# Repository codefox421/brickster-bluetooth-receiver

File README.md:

# BricksTer &ndash; Bluetooth Receiver

&nbsp;&nbsp;&nbsp;

The BricksTer Bluetooth Receiver lets you wirelessly control your LEGO creations from a smart phone, tablet, or PC. It is compatible with the NXT programmable brick. This repository houses the Eagle CAD schematic and design files for the printed circuit board along with the firmware for the receiver.

## Getting Started

### Part List

Components can be ordered from any distributor (e.g. DigiKey, Mouser, etc).
[Please see the Bill of Materials for the list of components.](https://github.com/BTbricks/brickster-bluetooth-receiver/blob/master/8884bt%20Remote%20Control%20Receiver/board/BOM.md)

The rev. 2 board can be purchased from OSH Park.
[Click here to view the OSH Park project page.](https://oshpark.com/shared_projects/jNrizzs2)

### Programming the Board

Once your board is soldered, use the Arduino IDE to load the firmware onto the microcontroller.
The IDE is available for free and can be downloaded from http://arduino.cc/main/software

#### Setting up the Arduino Environment

The microcontroller is an ATtiny84, which is not regularly supported by the Arduino IDE.
[Please visit the Arduino support page to learn more about using Arduino with the ATtiny84.](http://playground.arduino.cc/Main/ArduinoOnOtherAtmelChips)

Download the [Attiny 44/45/84/85 files](https://github.com/damellis/attiny/archive/master.zip) and extract them to `{ARDUINO}/hardware/`, where `{ARDUINO}` represents the directory into which the Arduino IDE and supporting files have been installed. Once completed, your directory should look like this:

```
{ARDUINO}
└-hardware
  └-attiny
    ├-boards.txt
    └-variants
      ├-tiny8
      | └-pins_arduino.h
      └-tiny14
        └-pins_arduino.h
```

#### Burning the "Bootloader"

The ATtiny84 comes from the factory running on an internal 1 MHz clock. In order to run the BricksTer firmware, the ATtiny84 must be told to use its interal 8 MHz clock.

* Connect your board to your computer via the programmer
* Apply power to the power-in Power Functions wire
* Open the Arduino IDE
* Ensure you have selected the proper serial port (`Tools > Serial Port`) and can communicate with the microcontroller
* Select `Tools > Board > ATtiny84 (internal 8 Mhz clock)`
* Select `Tools > Burn Bootloader`
* Wait for the programmer to finish, the IDE should display a success message

#### Loading the Firmware

* Connect your board to your computer via the programmer
* Apply power to the power-in Power Functions wire
* Open the Arduino IDE
* Ensure you have selected the proper serial port (`Tools > Serial Port`) and can communicate with the microcontroller
* Select `Tools > Board > ATtiny84 (internal 8 Mhz clock)`
* Open the firmware file, [`brickster8884bt.ino`](https://github.com/BTbricks/brickster-bluetooth-receiver/blob/master/8884bt%20Remote%20Control%20Receiver/firmware/brickster8884bt.ino)
* Click the Upload button on the Arduino IDE (circle with a right-pointing arrow)
* Wait for the the IDE and programmer to finish, the IDE should display a success message

Note: Use of a Atmel AVRISPmk2 programmer is strongly advised. Other programmers have been known to work, but we can only provide support for the AVRISPmk2.

### File Formats

Design files are created in CadSoft Eagle PCB Design Software.
A free version of the software can be downloaded from www.cadsoftusa.com

&nbsp;&nbsp;&nbsp;

## Ordering the PCB

You can order the unpopulated printed circuit board from OSH Park by following the link below.

<a href="https://oshpark.com/shared_projects/tWWWgV0f"></img></a>

## Distribution License

Where possible, this project uses the MIT license. [Please see the license file for full details.](https://github.com/BTbricks/brickster-bluetooth-receiver/blob/master/LICENSE)

## Contributing

The project is open to all issues and pull requests.
If you have any other questions or feedback, please [contact the project maintainers](https://github.com/orgs/BTbricks/members).

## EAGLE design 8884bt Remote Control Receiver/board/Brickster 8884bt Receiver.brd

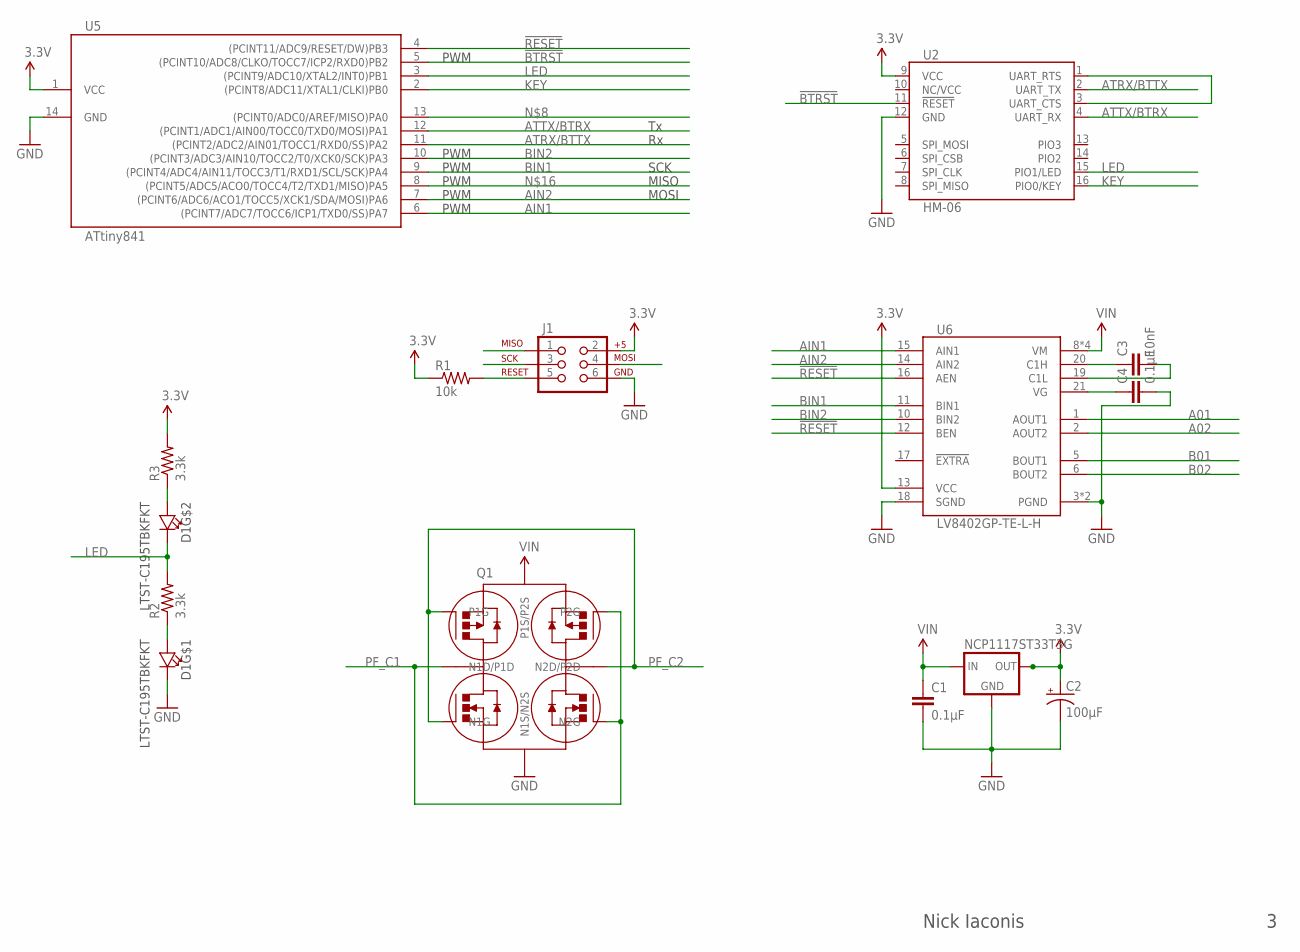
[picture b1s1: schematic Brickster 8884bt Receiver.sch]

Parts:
C1, C4: 0.1µF; 0402
C2: 100µF; 1206
C3: 10nF; 0402
D1: LTST-C195TBKFKT; CHIP-LTST
J1: AVR_SPI_PRG_6NS; 2X3-NS
NCP1117ST33T3G: IC_RT9164A; SOT223
Q1: DMHC3025LSD-13; SO8
R1: 10k; 0402; PARTNO ERJ-3GEYJ103V
R2, R3: 3.3k; 0402; PARTNO ERJ-3GEYJ103V
U2: HM-06; HM-05/06/07
U5: ATtiny841; 14SOICN
U6: LV8402GP-TE-L-H; VCT24

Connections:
3.3V: C2.1 (+), J1.2, NCP1117ST33T3G.2 (OUT), NCP1117ST33T3G.4, R1.1, R3.2, U2.9 (VCC), U5.1 (VCC), U6.13 (VCC)
!BTRST: U2.11 (!RESET), U5.5 ((PCINT10/ADC8/CLKO/TOCC7/ICP2/RXD0)PB2)
!RESET: J1.5, R1.2, U5.4 ((PCINT11/ADC9/RESET/DW)PB3), U6.12 (BEN), U6.16 (AEN)
A01: U6.1 (AOUT1)
A02: U6.2 (AOUT2)
AIN1: U5.6 ((PCINT7/ADC7/TOCC6/ICP1/TXD0/SS)PA7), U6.15 (AIN1)
AIN2: J1.4, U5.7 ((PCINT6/ADC6/ACO1/TOCC5/XCK1/SDA/MOSI)P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), U6.14 (AIN2)
ATRX/BTTX: U2.2 (UART_TX), U5.11 ((PCINT2/ADC2/AIN01/TOCC1/RXD0/SS)PA2)
ATTX/BTRX: U2.4 (UART_RX), U5.12 ((PCINT1/ADC1/AIN00/TOCC0/TXD0/MOSI)PA1)
B01: U6.5 (BOUT1)
B02: U6.6 (BOUT2)
BIN1: J1.3, U5.9 ((PCINT4/ADC4/AIN11/TOCC3/T1/RXD1/SCL/SC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), U6.11 (BIN1)
BIN2: U5.10 ((PCINT3/ADC3/AIN10/TOCC2/T0/XCK0/SCK)PA3), U6.10 (BIN2)
GND: C1.2, C2.2 (-), C4.2, D1.3, J1.6, NCP1117ST33T3G.1 (GND), Q1.P$3 (N1S/N2S), U2.12 (GND), U5.14 (GND), U6.3 (PGND), U6.4 (PGND), U6.18 (SGND)
KEY: U2.16 (PIO0/KEY), U5.2 ((PCINT8/ADC11/XTAL1/CLKI)PB0)
LED: D1.4, R2.2, U2.15 (PIO1/LED), U5.3 ((PCINT9/ADC10/XTAL2/INT0)PB1)
unnamed: D1.2, R3.1
unnamed: D1.1, R2.1
unnamed: U2.1 (UART_RTS), U2.3 (UART_CTS)
unnamed: C3.2, U6.19 (C1L)
unnamed: C4.1, U6.21 (VG)
unnamed: C3.1, U6.20 (C1H)
unnamed: J1.1, U5.8 ((PCINT5/ADC5/ACO0/TOCC4/T2/TXD1/MISO)PA5)
PF_C1: Q1.P$2 (N1D/P1D), Q1.P$4 (N2G), Q1.P$5 (P2G)
PF_C2: Q1.P$1 (N1G), Q1.P$6 (N2D/P2D), Q1.P$8 (P1G)
VIN: C1.1, NCP1117ST33T3G.3 (IN), Q1.P$7 (P1S/P2S), U6.8 (VM), U6.9 (VM), U6.22 (VM), U6.23 (VM)

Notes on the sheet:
Nick Iaconis
PWM
SCK
MISO
MOSI

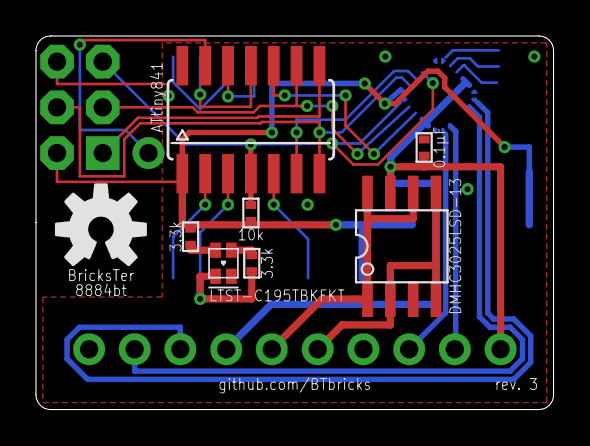
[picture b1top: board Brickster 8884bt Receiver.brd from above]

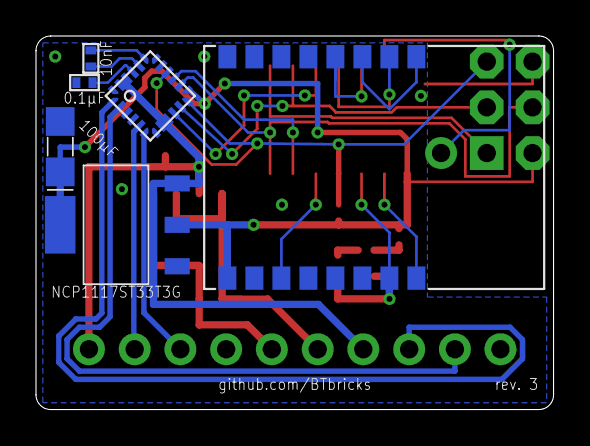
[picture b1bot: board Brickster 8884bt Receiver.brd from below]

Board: 2 copper layers, 28.8 x 20.8 mm, 15 parts (6 on the bottom side), 22 nets.

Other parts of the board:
LOGO1: OSHW-LOGOM; OSHW-LOGO-M

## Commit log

2015-07-20 Ensure HC-06 is enabled on boot
2016-02-15 Move ino file into a sketch directory
    This will allow Arduino IDE to open it in place.
2016-02-15 Update gitignore
2016-02-15 Update library
2016-02-15 Ensure Bluetooth module is enabled on boot
    Without explicitly writing HIGH to the !BTRST line, the module could be
    in reset mode.
2016-02-15 Update DRC file
2016-02-15 Update receiver to revision 3
2016-03-03 Update firmware for revision 3

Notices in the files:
parts and their libraries:
SparkFun-Connectors: Licensing: CC v3.0 Share-Alike You are welcome to use this library for commercial purposes.
